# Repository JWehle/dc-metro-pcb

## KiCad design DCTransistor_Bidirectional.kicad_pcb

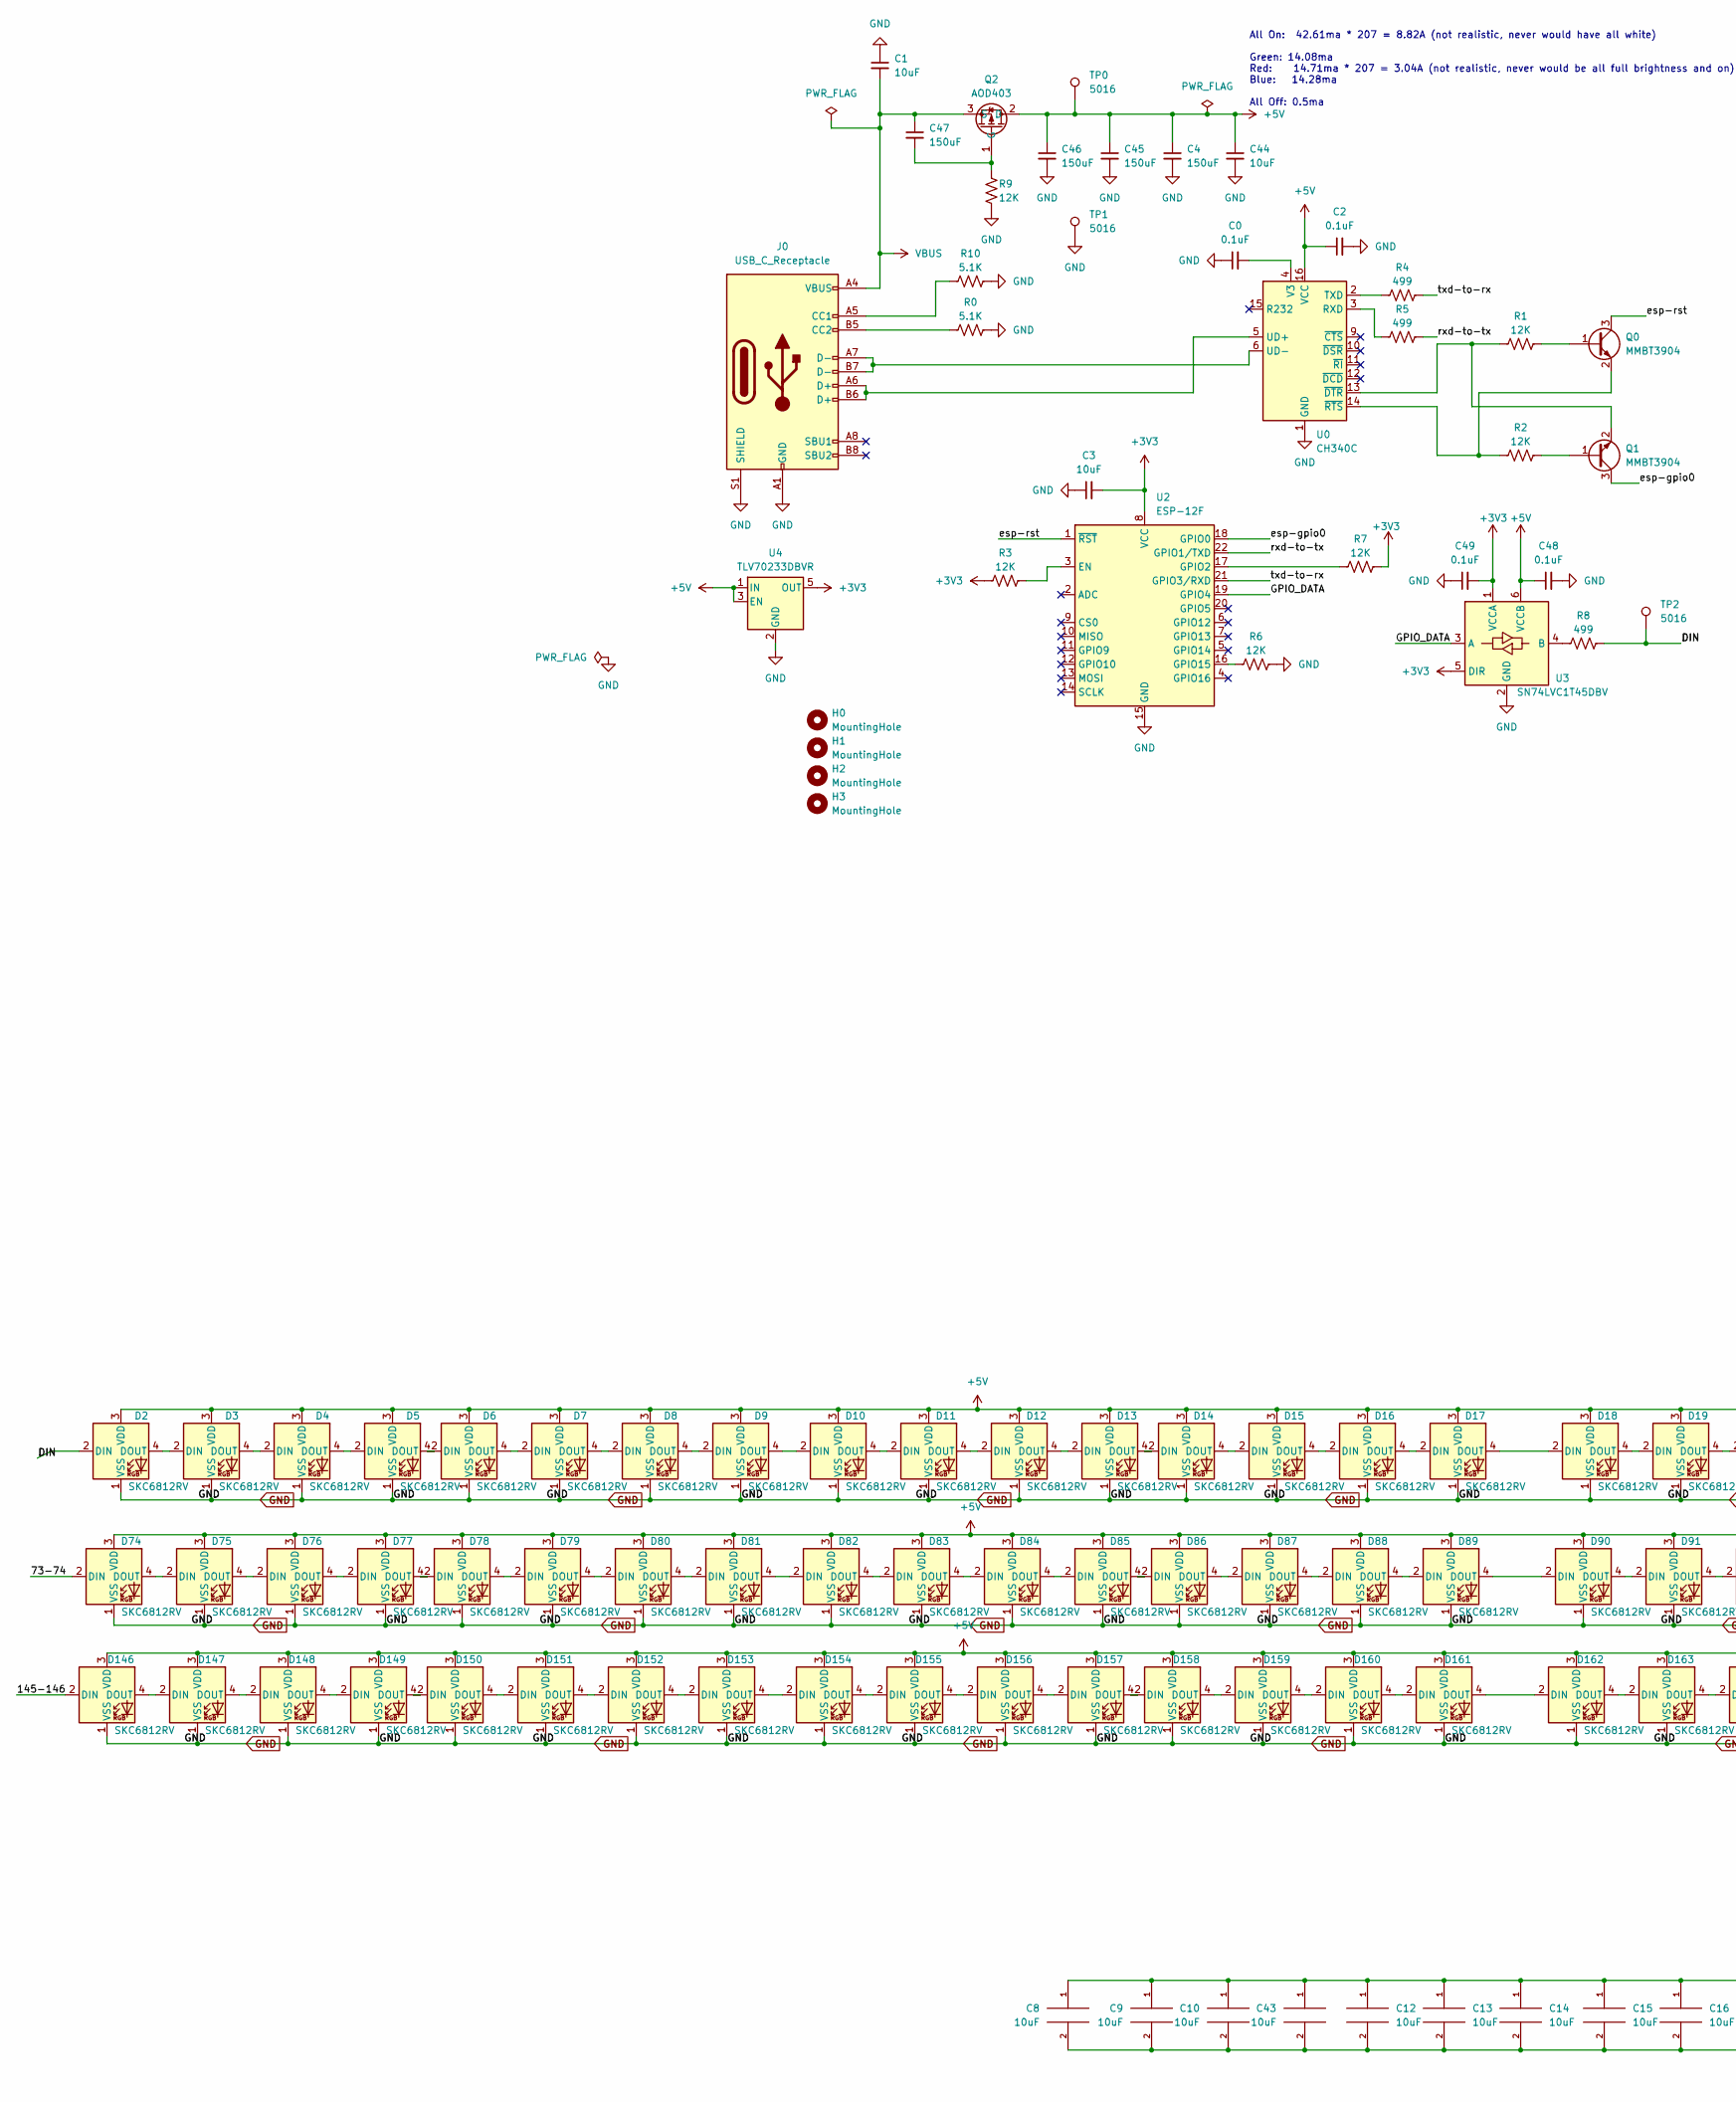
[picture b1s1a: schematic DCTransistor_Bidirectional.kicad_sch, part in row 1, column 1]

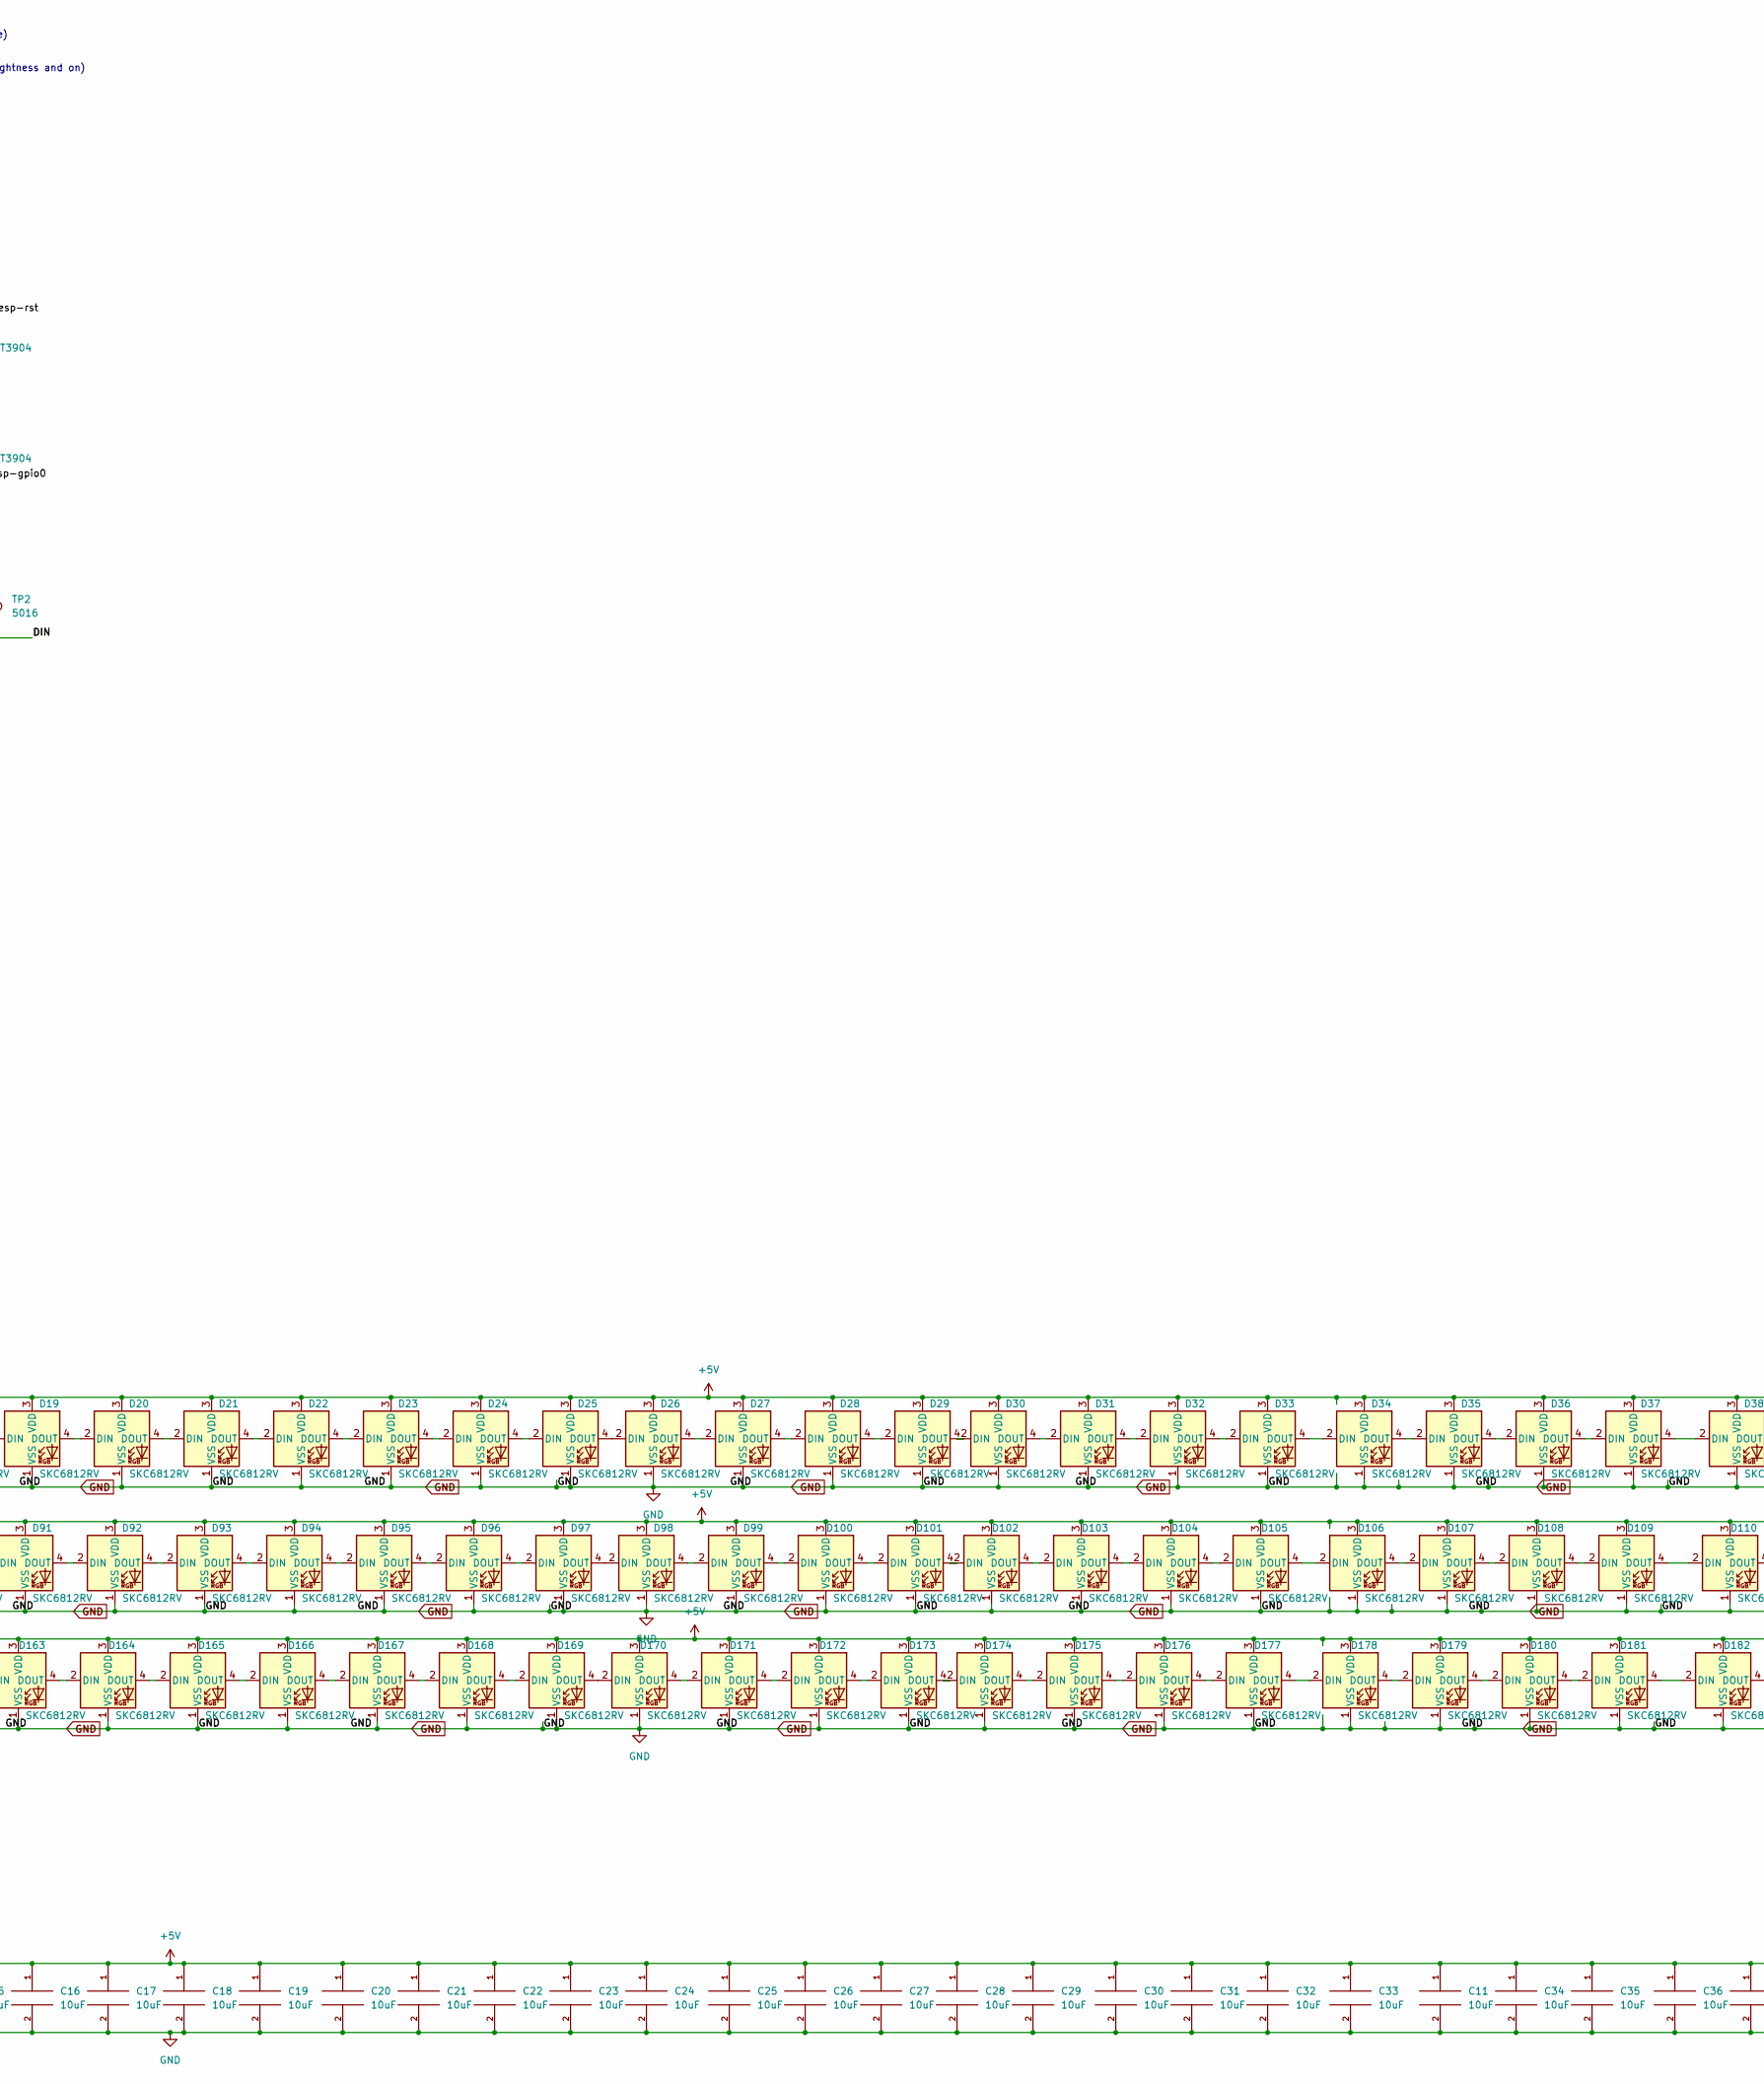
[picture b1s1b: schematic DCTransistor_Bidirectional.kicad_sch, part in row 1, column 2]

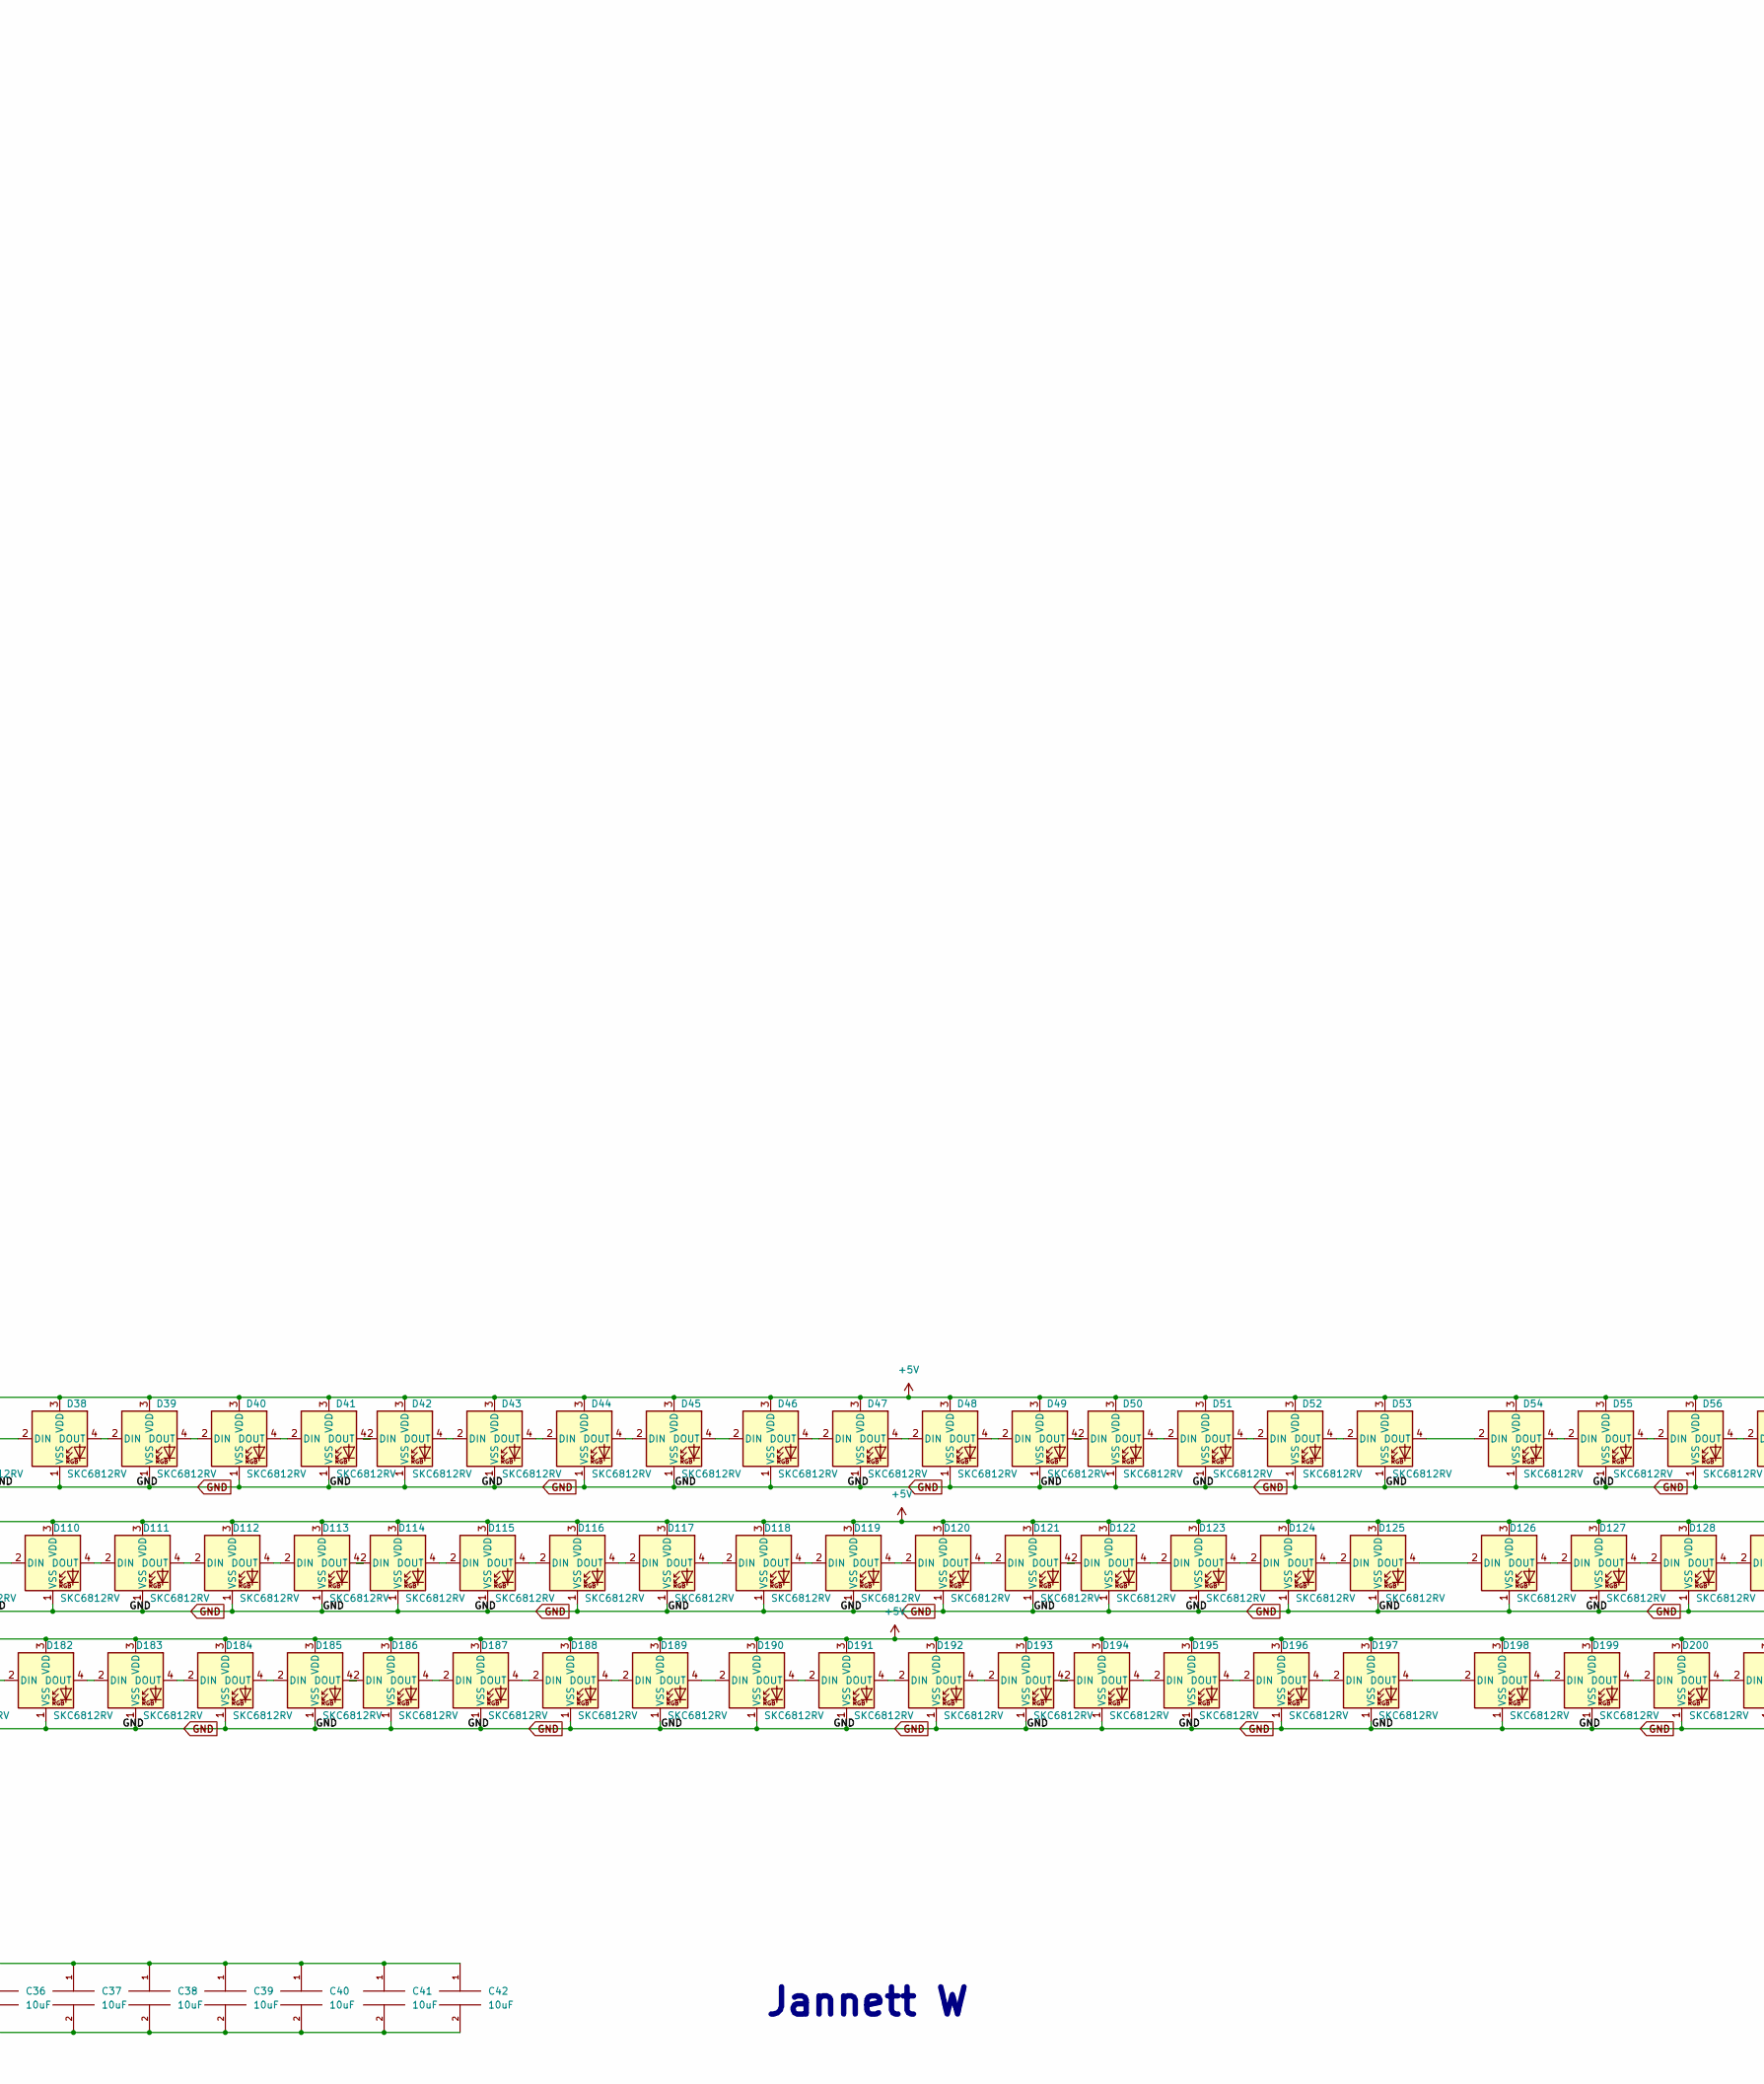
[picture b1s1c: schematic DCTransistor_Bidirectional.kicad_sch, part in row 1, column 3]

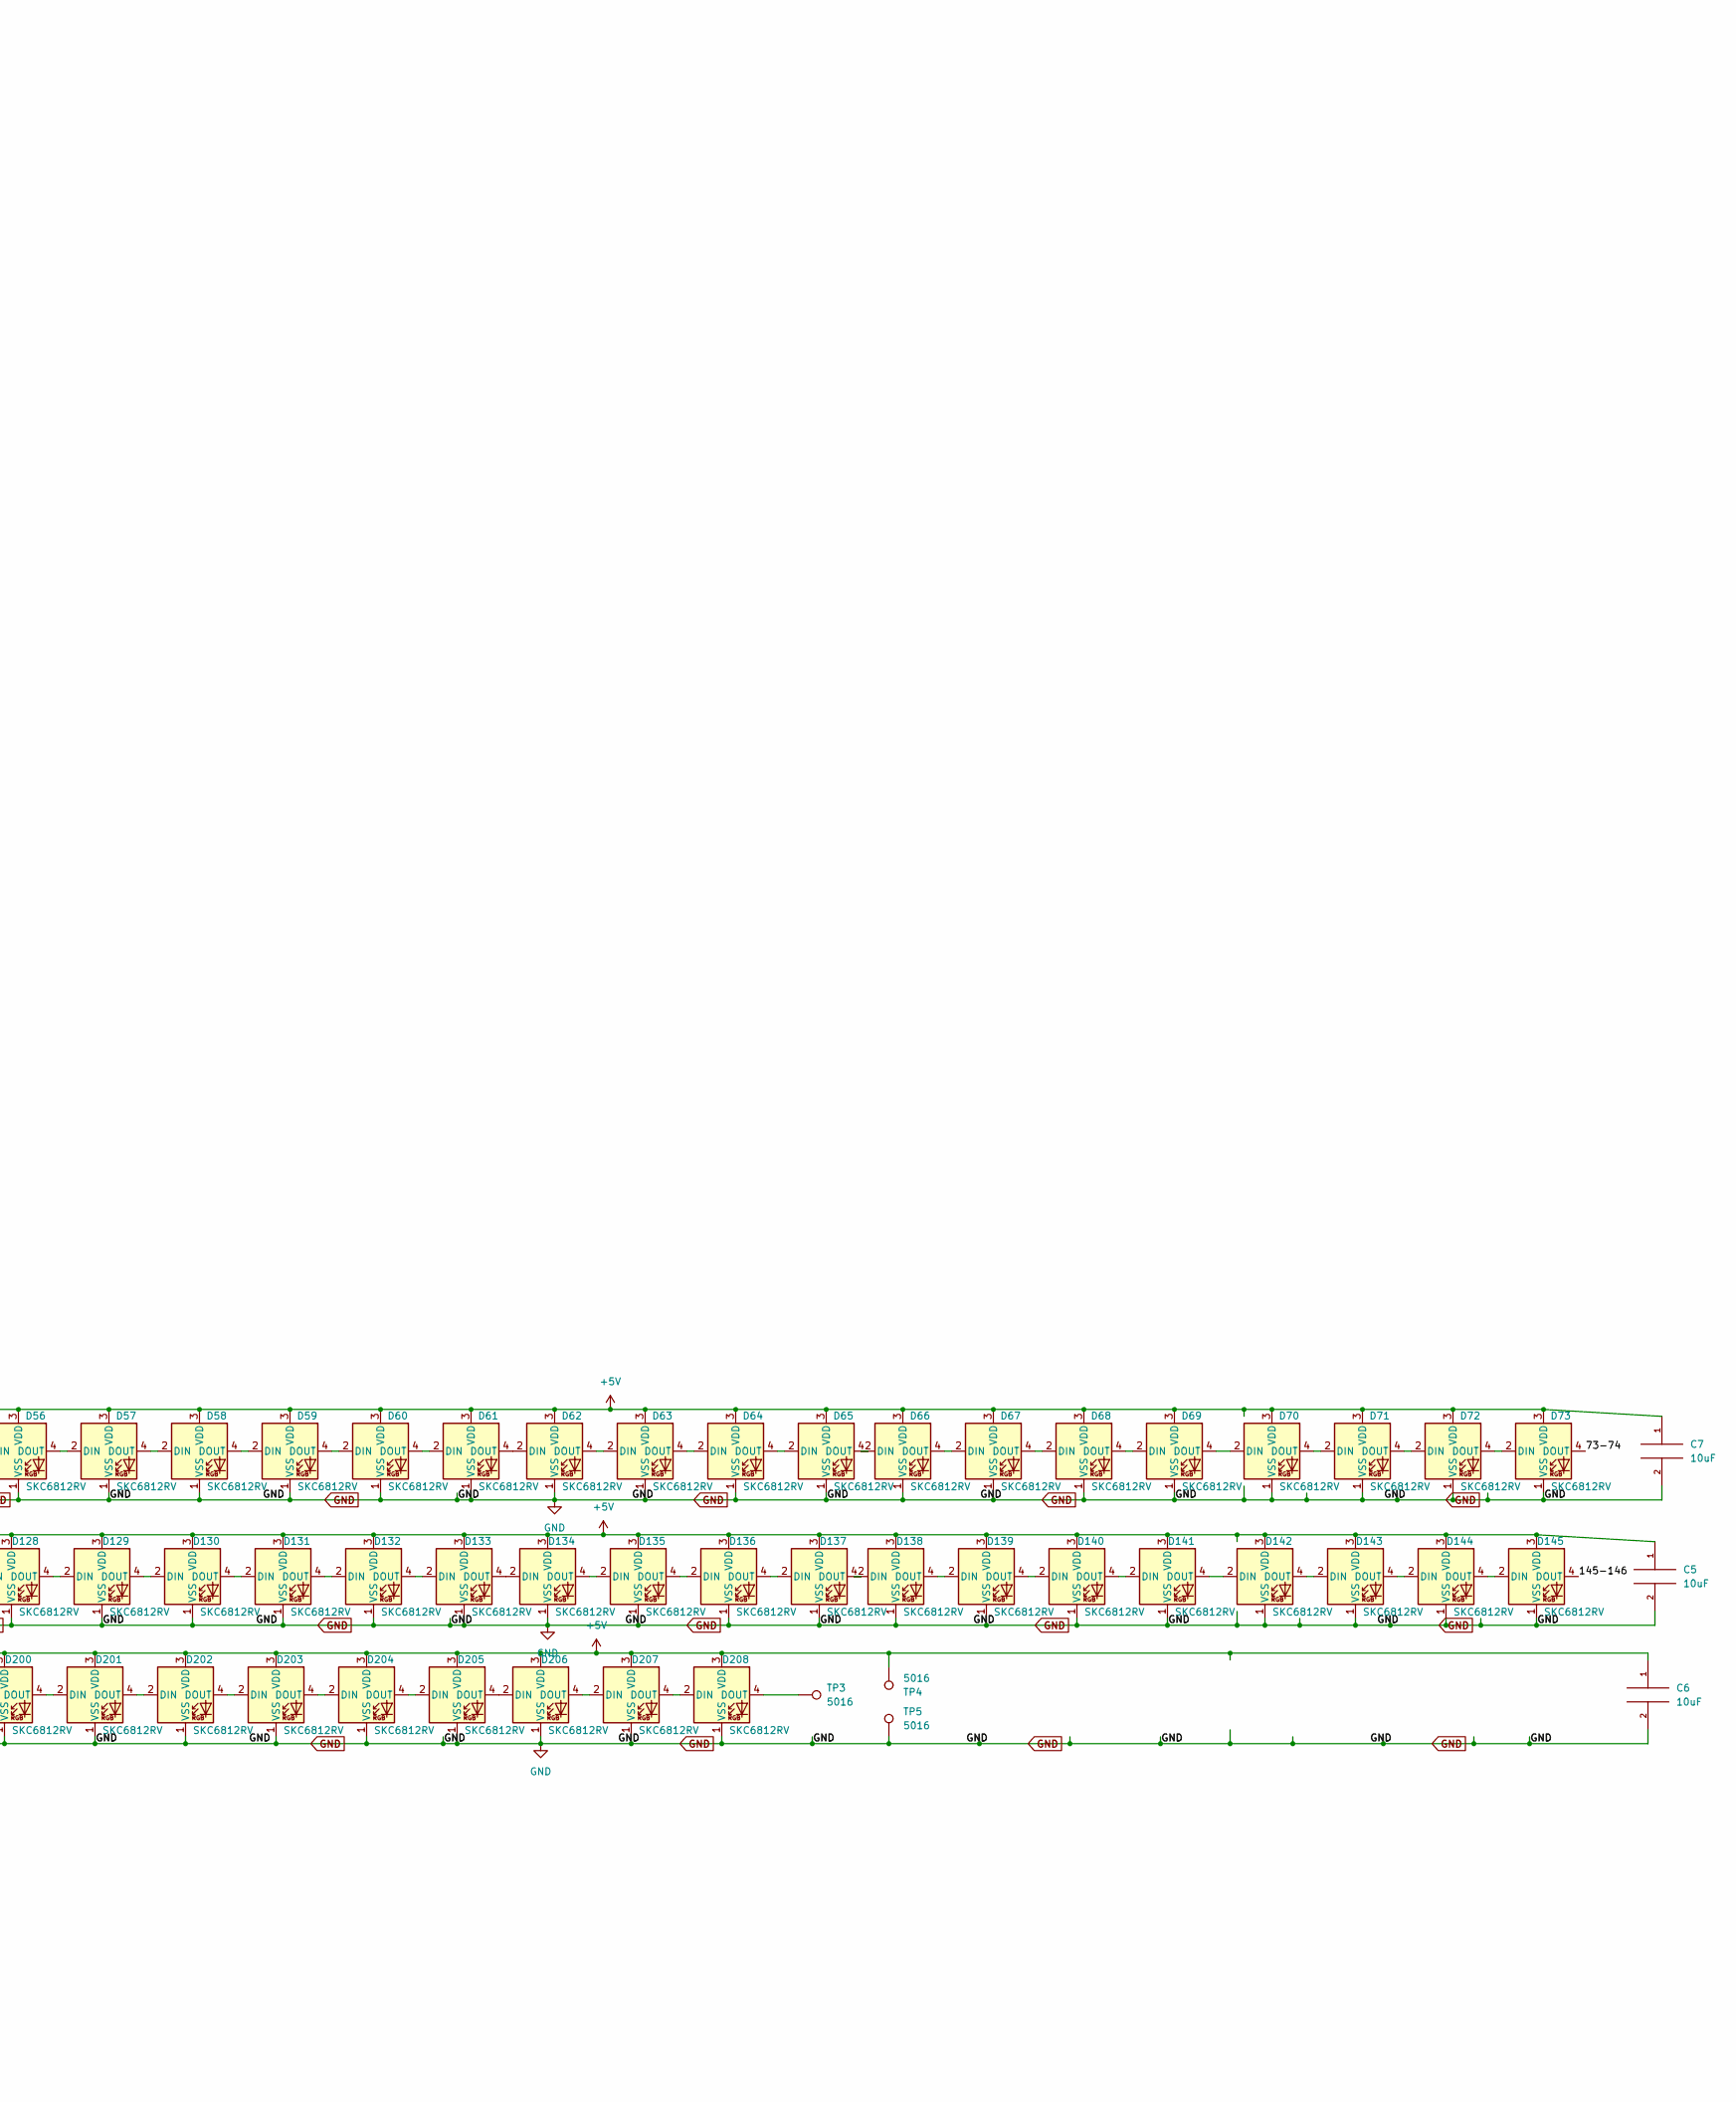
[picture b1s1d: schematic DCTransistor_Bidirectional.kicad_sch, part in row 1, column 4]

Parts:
C0, C2, C48, C49: 0.1uF; C_0603_1608Metric
C1, C3, C5, C6, C7, C8, C9, C10, C11, C12, C13, C14, C15, C16, C17, C18, C19, C20, C21, C22, C23, C24, C25, C26, C27, C28, C29, C30, C31, C32, C33, C34, C35, C36, C37, C38, C39, C40, C41, C42, C43, C44: 10uF; C_0603_1608Metric
C4, C45, C46, C47: 150uF; CP_EIA-7343-43_Kemet-X_Pad2.25x2.55mm_HandSolder
D2, D3, D4, D5, D6, D7, D8, D9, D10, D11, D12, D13, D14, D15, D16, D17, D18, D19, D20, D21, D22, D23, D24, D25, D26, D27, D28, D29, D30, D31, D32, D33, D34, D35, D36, D37, D38, D39, D40, D41, D42, D43, D44, D45, D46, D47, D48, D49, D50, D51, D52, D53, D54, D55, D56, D57, D58, D59, D60, D61, D62, D63, D64, D65, D66, D67, D68, D69, D70, D71, D72, D73, D74, D75, D76, D77, D78, D79, D80, D81, D82, D83, D84, D85, D86, D87, D88, D89, D90, D91, D92, D93, D94, D95, D96, D97, D98, D99, D100, D101, D102, D103, D104, D105, D106, D107, D108, D109, D110, D111, D112, D113, D114, D115, D116, D117, D118, D119, D120, D121, D122, D123, D124, D125, D126, D127, D128, D129, D130, D131, D132, D133, D134, D135, D136, D137, D138, D139, D140, D141, D142, D143, D144, D145, D146, D147, D148, D149, D150, D151, D152, D153, D154, D155, D156, D157, D158, D159, D160, D161, D162, D163, D164, D165, D166, D167, D168, D169, D170, D171, D172, D173, D174, D175, D176, D177, D178, D179, D180, D181, D182, D183, D184, D185, D186, D187, D188, D189, D190, D191, D192, D193, D194, D195, D196, D197, D198, D199, D200, D201, D202, D203, D204, D205, D206, D207, D208: SKC6812RV; LED_SK6812_PLCC4_5.0x5.0mm_P3.2mm_no_silk
H0, H1, H2, H3: MountingHole; MountingHole_6.4mm_M6
J0: USB_C_Receptacle; USB_C_Receptacle_GSB1C4621DS2HR
Q0, Q1: MMBT3904; SOT-23-3
Q2: AOD403; TO-252-2
R0, R10: 5.1K; R_0603_1608Metric
R1, R2, R3, R6, R7, R9: 12K; R_0603_1608Metric
R4, R5, R8: 499; R_0603_1608Metric
TP0, TP1, TP2, TP3, TP4, TP5: 5016; TestPoint_Keystone_5016_Compact
U0: CH340C; SOIC-16_3.9x9.9mm_P1.27mm
U2: ESP-12F; ESP-12E
U3: SN74LVC1T45DBV; SOT-23-6_Handsoldering
U4: TLV70233DBVR; SOT-23-5

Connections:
+3V3: C3.2, C49.2, R3.1, R7.2, U2.8 (VCC), U3.1 (VCCA), U3.5 (DIR), U4.5 (OUT)
+5V: C2.1, C4.1, C5.1, C6.1, C7.1, C8.1, C9.1, C10.1, C11.1, C12.1, C13.1, C14.1, C15.1, C16.1, C17.1, C18.1, C19.1, C20.1, C21.1, C22.1, C23.1, C24.1, C25.1, C26.1, C27.1, C28.1, C29.1, C30.1, C31.1, C32.1, C33.1, C34.1, C35.1, C36.1, C37.1, C38.1, C39.1, C40.1, C41.1, C42.1, C43.1, C44.1, C45.1, C46.1, C48.1, D2.3 (VDD), D3.3 (VDD), D4.3 (VDD), D5.3 (VDD), D6.3 (VDD), D7.3 (VDD), D8.3 (VDD), D9.3 (VDD), D10.3 (VDD), D11.3 (VDD), D12.3 (VDD), D13.3 (VDD), D14.3 (VDD), D15.3 (VDD), D16.3 (VDD), D17.3 (VDD), D18.3 (VDD), D19.3 (VDD), D20.3 (VDD), D21.3 (VDD), D22.3 (VDD), D23.3 (VDD), D24.3 (VDD), D25.3 (VDD), D26.3 (VDD), D27.3 (VDD), D28.3 (VDD), D29.3 (VDD), D30.3 (VDD), D31.3 (VDD), D32.3 (VDD), D33.3 (VDD), D34.3 (VDD), D35.3 (VDD), D36.3 (VDD), D37.3 (VDD), D38.3 (VDD), D39.3 (VDD), D40.3 (VDD), D41.3 (VDD), D42.3 (VDD), D43.3 (VDD), D44.3 (VDD), D45.3 (VDD), D46.3 (VDD), D47.3 (VDD), D48.3 (VDD), D49.3 (VDD), D50.3 (VDD), D51.3 (VDD), D52.3 (VDD), D53.3 (VDD), D54.3 (VDD)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
/73-74: D73.4 (DOUT), D74.2 (DIN)
/145-146: D145.4 (DOUT), D146.2 (DIN)
/DIN: D2.2 (DIN), R8.2, TP2.1
/GPIO_DATA: U2.19 (GPIO4), U3.3 (A)
/esp-gpio0: Q1.3 (C), U2.18 (GPIO0)
/esp-rst: Q0.3 (C), U2.1 (~RST)
/rxd-to-tx: R5.2, U2.22 (GPIO1/TXD)
/txd-to-rx: R4.2, U2.21 (GPIO3/RXD)
GND: C0.1, C1.1, C2.2, C3.1, C4.2, C5.2, C6.2, C7.2, C8.2, C9.2, C10.2, C11.2, C12.2, C13.2, C14.2, C15.2, C16.2, C17.2, C18.2, C19.2, C20.2, C21.2, C22.2, C23.2, C24.2, C25.2, C26.2, C27.2, C28.2, C29.2, C30.2, C31.2, C32.2, C33.2, C34.2, C35.2, C36.2, C37.2, C38.2, C39.2, C40.2, C41.2, C42.2, C43.2, C44.2, C45.2, C46.2, C48.2, C49.1, D2.1 (VSS), D3.1 (VSS), D4.1 (VSS), D5.1 (VSS), D6.1 (VSS), D7.1 (VSS), D8.1 (VSS), D9.1 (VSS), D10.1 (VSS), D11.1 (VSS), D12.1 (VSS), D13.1 (VSS), D14.1 (VSS), D15.1 (VSS), D16.1 (VSS), D17.1 (VSS), D18.1 (VSS), D19.1 (VSS), D20.1 (VSS), D21.1 (VSS), D22.1 (VSS), D23.1 (VSS), D24.1 (VSS), D25.1 (VSS), D26.1 (VSS), D27.1 (VSS), D28.1 (VSS), D29.1 (VSS), D30.1 (VSS), D31.1 (VSS), D32.1 (VSS), D33.1 (VSS), D34.1 (VSS), D35.1 (VSS), D36.1 (VSS), D37.1 (VSS), D38.1 (VSS), D39.1 (VSS), D40.1 (VSS), D41.1 (VSS), D42.1 (VSS), D43.1 (VSS), D44.1 (VSS), D45.1 (VSS), D46.1 (VSS), D47.1 (VSS), D48.1 (VSS), D49.1 (VSS), D50.1 (VSS)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
unnamed: D2.4 (DOUT), D3.2 (DIN)
unnamed: D3.4 (DOUT), D4.2 (DIN)
unnamed: D4.4 (DOUT), D5.2 (DIN)
unnamed: D5.4 (DOUT), D6.2 (DIN)
unnamed: D6.4 (DOUT), D7.2 (DIN)
unnamed: D7.4 (DOUT), D8.2 (DIN)
unnamed: D8.4 (DOUT), D9.2 (DIN)
unnamed: D9.4 (DOUT), D10.2 (DIN)
unnamed: D10.4 (DOUT), D11.2 (DIN)
unnamed: D11.4 (DOUT), D12.2 (DIN)
unnamed: D12.4 (DOUT), D13.2 (DIN)
unnamed: D13.4 (DOUT), D14.2 (DIN)
unnamed: D14.4 (DOUT), D15.2 (DIN)
unnamed: D15.4 (DOUT), D16.2 (DIN)
unnamed: D16.4 (DOUT), D17.2 (DIN)
unnamed: D17.4 (DOUT), D18.2 (DIN)
unnamed: D18.4 (DOUT), D19.2 (DIN)
unnamed: D19.4 (DOUT), D20.2 (DIN)
unnamed: D20.4 (DOUT), D21.2 (DIN)
unnamed: D21.4 (DOUT), D22.2 (DIN)
unnamed: D22.4 (DOUT), D23.2 (DIN)
unnamed: D23.4 (DOUT), D24.2 (DIN)
unnamed: D24.4 (DOUT), D25.2 (DIN)
unnamed: D25.4 (DOUT), D26.2 (DIN)
unnamed: D26.4 (DOUT), D27.2 (DIN)
unnamed: D27.4 (DOUT), D28.2 (DIN)
unnamed: D28.4 (DOUT), D29.2 (DIN)
unnamed: D29.4 (DOUT), D30.2 (DIN)
unnamed: D30.4 (DOUT), D31.2 (DIN)
unnamed: D31.4 (DOUT), D32.2 (DIN)
unnamed: D32.4 (DOUT), D33.2 (DIN)
unnamed: D33.4 (DOUT), D34.2 (DIN)
unnamed: D34.4 (DOUT), D35.2 (DIN)
unnamed: D35.4 (DOUT), D36.2 (DIN)
unnamed: D36.4 (DOUT), D37.2 (DIN)
unnamed: D37.4 (DOUT), D38.2 (DIN)
unnamed: D38.4 (DOUT), D39.2 (DIN)
unnamed: D39.4 (DOUT), D40.2 (DIN)
unnamed: D40.4 (DOUT), D41.2 (DIN)
unnamed: D41.4 (DOUT), D42.2 (DIN)
unnamed: D42.4 (DOUT), D43.2 (DIN)
unnamed: D43.4 (DOUT), D44.2 (DIN)
unnamed: D44.4 (DOUT), D45.2 (DIN)
unnamed: D45.4 (DOUT), D46.2 (DIN)
unnamed: D46.4 (DOUT), D47.2 (DIN)
unnamed: D47.4 (DOUT), D48.2 (DIN)
unnamed: D48.4 (DOUT), D49.2 (DIN)
unnamed: D49.4 (DOUT), D50.2 (DIN)
unnamed: D50.4 (DOUT), D51.2 (DIN)
unnamed: D51.4 (DOUT), D52.2 (DIN)
unnamed: D52.4 (DOUT), D53.2 (DIN)
unnamed: D53.4 (DOUT), D54.2 (DIN)
unnamed: D54.4 (DOUT), D55.2 (DIN)
unnamed: D55.4 (DOUT), D56.2 (DIN)
unnamed: D56.4 (DOUT), D57.2 (DIN)
unnamed: D57.4 (DOUT), D58.2 (DIN)
unnamed: D58.4 (DOUT), D59.2 (DIN)
unnamed: D59.4 (DOUT), D60.2 (DIN)
unnamed: D60.4 (DOUT), D61.2 (DIN)
unnamed: D61.4 (DOUT), D62.2 (DIN)
unnamed: D62.4 (DOUT), D63.2 (DIN)
unnamed: D63.4 (DOUT), D64.2 (DIN)
unnamed: D64.4 (DOUT), D65.2 (DIN)
unnamed: D65.4 (DOUT), D66.2 (DIN)
unnamed: D66.4 (DOUT), D67.2 (DIN)
unnamed: D67.4 (DOUT), D68.2 (DIN)
unnamed: D68.4 (DOUT), D69.2 (DIN)
unnamed: D69.4 (DOUT), D70.2 (DIN)
unnamed: D70.4 (DOUT), D71.2 (DIN)
unnamed: D71.4 (DOUT), D72.2 (DIN)
unnamed: D72.4 (DOUT), D73.2 (DIN)
unnamed: D74.4 (DOUT), D75.2 (DIN)
unnamed: D75.4 (DOUT), D76.2 (DIN)
unnamed: D76.4 (DOUT), D77.2 (DIN)
unnamed: D77.4 (DOUT), D78.2 (DIN)
unnamed: D78.4 (DOUT), D79.2 (DIN)
unnamed: D79.4 (DOUT), D80.2 (DIN)
unnamed: D80.4 (DOUT), D81.2 (DIN)
unnamed: D81.4 (DOUT), D82.2 (DIN)
unnamed: D82.4 (DOUT), D83.2 (DIN)
unnamed: D83.4 (DOUT), D84.2 (DIN)
unnamed: D84.4 (DOUT), D85.2 (DIN)
unnamed: D85.4 (DOUT), D86.2 (DIN)
unnamed: D86.4 (DOUT), D87.2 (DIN)
unnamed: D87.4 (DOUT), D88.2 (DIN)
unnamed: D88.4 (DOUT), D89.2 (DIN)
unnamed: D89.4 (DOUT), D90.2 (DIN)
unnamed: D90.4 (DOUT), D91.2 (DIN)
unnamed: D91.4 (DOUT), D92.2 (DIN)
unnamed: D92.4 (DOUT), D93.2 (DIN)
unnamed: D93.4 (DOUT), D94.2 (DIN)
unnamed: D94.4 (DOUT), D95.2 (DIN)
unnamed: D95.4 (DOUT), D96.2 (DIN)
unnamed: D96.4 (DOUT), D97.2 (DIN)
unnamed: D97.4 (DOUT), D98.2 (DIN)
unnamed: D98.4 (DOUT), D99.2 (DIN)
unnamed: D99.4 (DOUT), D100.2 (DIN)
unnamed: D100.4 (DOUT), D101.2 (DIN)
unnamed: D101.4 (DOUT), D102.2 (DIN)
unnamed: D102.4 (DOUT), D103.2 (DIN)
unnamed: D103.4 (DOUT), D104.2 (DIN)
unnamed: D104.4 (DOUT), D105.2 (DIN)
unnamed: D105.4 (DOUT), D106.2 (DIN)
unnamed: D106.4 (DOUT), D107.2 (DIN)
unnamed: D107.4 (DOUT), D108.2 (DIN)
unnamed: D108.4 (DOUT), D109.2 (DIN)
unnamed: D109.4 (DOUT), D110.2 (DIN)
unnamed: D110.4 (DOUT), D111.2 (DIN)
unnamed: D111.4 (DOUT), D112.2 (DIN)
unnamed: D112.4 (DOUT), D113.2 (DIN)
unnamed: D113.4 (DOUT), D114.2 (DIN)
unnamed: D114.4 (DOUT), D115.2 (DIN)
unnamed: D115.4 (DOUT), D116.2 (DIN)
unnamed: D116.4 (DOUT), D117.2 (DIN)
unnamed: D117.4 (DOUT), D118.2 (DIN)
unnamed: D118.4 (DOUT), D119.2 (DIN)
unnamed: D119.4 (DOUT), D120.2 (DIN)
unnamed: D120.4 (DOUT), D121.2 (DIN)
unnamed: D121.4 (DOUT), D122.2 (DIN)
unnamed: D122.4 (DOUT), D123.2 (DIN)
unnamed: D123.4 (DOUT), D124.2 (DIN)
unnamed: D124.4 (DOUT), D125.2 (DIN)
unnamed: D125.4 (DOUT), D126.2 (DIN)
unnamed: D126.4 (DOUT), D127.2 (DIN)
unnamed: D127.4 (DOUT), D128.2 (DIN)
unnamed: D128.4 (DOUT), D129.2 (DIN)
unnamed: D129.4 (DOUT), D130.2 (DIN)
unnamed: D130.4 (DOUT), D131.2 (DIN)
unnamed: D131.4 (DOUT), D132.2 (DIN)
unnamed: D132.4 (DOUT), D133.2 (DIN)
unnamed: D133.4 (DOUT), D134.2 (DIN)
unnamed: D134.4 (DOUT), D135.2 (DIN)
unnamed: D135.4 (DOUT), D136.2 (DIN)
unnamed: D136.4 (DOUT), D137.2 (DIN)
unnamed: D137.4 (DOUT), D138.2 (DIN)
unnamed: D138.4 (DOUT), D139.2 (DIN)
unnamed: D139.4 (DOUT), D140.2 (DIN)
unnamed: D140.4 (DOUT), D141.2 (DIN)
unnamed: D141.4 (DOUT), D142.2 (DIN)
unnamed: D142.4 (DOUT), D143.2 (DIN)
unnamed: D143.4 (DOUT), D144.2 (DIN)
unnamed: D144.4 (DOUT), D145.2 (DIN)
unnamed: D146.4 (DOUT), D147.2 (DIN)
unnamed: D147.4 (DOUT), D148.2 (DIN)
unnamed: D148.4 (DOUT), D149.2 (DIN)
unnamed: D149.4 (DOUT), D150.2 (DIN)
unnamed: D150.4 (DOUT), D151.2 (DIN)
unnamed: D151.4 (DOUT), D152.2 (DIN)
unnamed: D152.4 (DOUT), D153.2 (DIN)
unnamed: D153.4 (DOUT), D154.2 (DIN)
unnamed: D154.4 (DOUT), D155.2 (DIN)
unnamed: D155.4 (DOUT), D156.2 (DIN)
unnamed: D156.4 (DOUT), D157.2 (DIN)
unnamed: D157.4 (DOUT), D158.2 (DIN)
unnamed: D158.4 (DOUT), D159.2 (DIN)
unnamed: D159.4 (DOUT), D160.2 (DIN)
unnamed: D160.4 (DOUT), D161.2 (DIN)
unnamed: D161.4 (DOUT), D162.2 (DIN)
unnamed: D162.4 (DOUT), D163.2 (DIN)
unnamed: D163.4 (DOUT), D164.2 (DIN)
unnamed: D164.4 (DOUT), D165.2 (DIN)
unnamed: D165.4 (DOUT), D166.2 (DIN)
unnamed: D166.4 (DOUT), D167.2 (DIN)
unnamed: D167.4 (DOUT), D168.2 (DIN)
unnamed: D168.4 (DOUT), D169.2 (DIN)
unnamed: D169.4 (DOUT), D170.2 (DIN)
unnamed: D170.4 (DOUT), D171.2 (DIN)
unnamed: D171.4 (DOUT), D172.2 (DIN)
unnamed: D172.4 (DOUT), D173.2 (DIN)
unnamed: D173.4 (DOUT), D174.2 (DIN)
unnamed: D174.4 (DOUT), D175.2 (DIN)
unnamed: D175.4 (DOUT), D176.2 (DIN)
unnamed: D176.4 (DOUT), D177.2 (DIN)
unnamed: D177.4 (DOUT), D178.2 (DIN)
unnamed: D178.4 (DOUT), D179.2 (DIN)
unnamed: D179.4 (DOUT), D180.2 (DIN)
unnamed: D180.4 (DOUT), D181.2 (DIN)
unnamed: D181.4 (DOUT), D182.2 (DIN)
unnamed: D182.4 (DOUT), D183.2 (DIN)
unnamed: D183.4 (DOUT), D184.2 (DIN)
unnamed: D184.4 (DOUT), D185.2 (DIN)
unnamed: D185.4 (DOUT), D186.2 (DIN)
unnamed: D186.4 (DOUT), D187.2 (DIN)
unnamed: D187.4 (DOUT), D188.2 (DIN)
unnamed: D188.4 (DOUT), D189.2 (DIN)
unnamed: D189.4 (DOUT), D190.2 (DIN)
unnamed: D190.4 (DOUT), D191.2 (DIN)
unnamed: D191.4 (DOUT), D192.2 (DIN)
unnamed: D192.4 (DOUT), D193.2 (DIN)
unnamed: D193.4 (DOUT), D194.2 (DIN)
unnamed: D194.4 (DOUT), D195.2 (DIN)
unnamed: D195.4 (DOUT), D196.2 (DIN)
unnamed: D196.4 (DOUT), D197.2 (DIN)
unnamed: D197.4 (DOUT), D198.2 (DIN)
unnamed: D198.4 (DOUT), D199.2 (DIN)
unnamed: D199.4 (DOUT), D200.2 (DIN)
unnamed: D200.4 (DOUT), D201.2 (DIN)
unnamed: D201.4 (DOUT), D202.2 (DIN)
unnamed: D202.4 (DOUT), D203.2 (DIN)
unnamed: D203.4 (DOUT), D204.2 (DIN)
unnamed: D204.4 (DOUT), D205.2 (DIN)
unnamed: D205.4 (DOUT), D206.2 (DIN)
unnamed: D206.4 (DOUT), D207.2 (DIN)
unnamed: D207.4 (DOUT), D208.2 (DIN)
unnamed: D208.4 (DOUT), TP3.1
unnamed: J0.A5 (CC1), R10.1
unnamed: J0.B5 (CC2), R0.1
unnamed: Q0.1 (B), R1.2
unnamed: Q0.2 (E), R2.1, U0.14 (~RTS)
unnamed: Q1.1 (B), R2.2
unnamed: Q1.2 (E), R1.1, U0.13 (~DTR)
unnamed: C47.2, Q2.1 (G), R9.1
unnamed: R5.1, U0.3 (RXD)
unnamed: R4.1, U0.2 (TXD)
unnamed: J0.A6 (D+), J0.B6 (D+), U0.5 (UD+)
unnamed: J0.A7 (D-), J0.B7 (D-), U0.6 (UD-)
unnamed: C0.2, U0.4 (V3)
unnamed: R3.2, U2.3 (EN)
unnamed: R7.1, U2.17 (GPIO2)
unnamed: R6.1, U2.16 (GPIO15)
unnamed: R8.1, U3.4 (B)
VBUS: C1.2, C47.1, J0.A4 (VBUS), J0.A9 (VBUS), J0.B4 (VBUS), J0.B9 (VBUS), Q2.3 (S)

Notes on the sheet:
All On: 42.61ma * 207 = 8.82A (not realistic, never would have all white) Green: 14.08ma Red: 14.71ma * 207 = 3.04A (not realistic, never would be all full brightness and on) Blue: 14.28ma All Off: 0.5ma
Jannett W

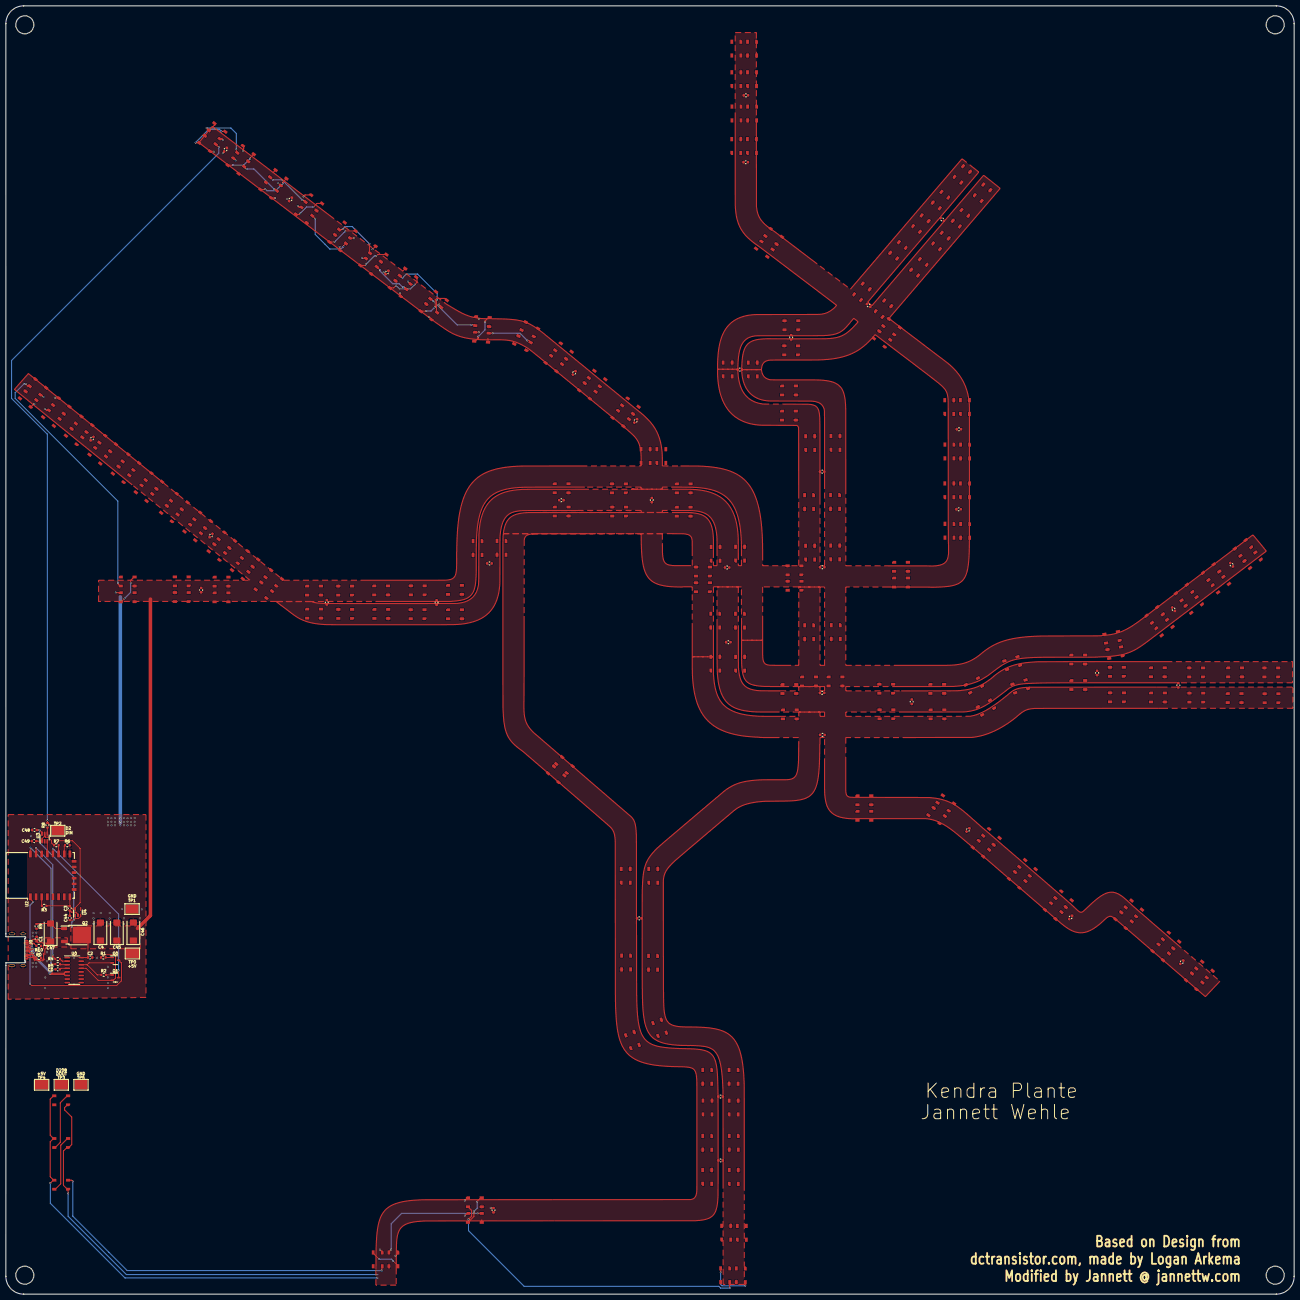
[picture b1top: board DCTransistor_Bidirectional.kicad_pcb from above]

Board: 2 copper layers, 457.2 x 457.2 mm, 286 parts (0 on the bottom side), 233 nets.

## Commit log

2025-01-25 schematic changes
2025-02-03 removed graphic temporarily for layout
2025-02-08 recentered pcb
2025-02-08 layout edits
2025-02-09 layout and footprint changes
2025-02-10 more layout updates
2025-03-16 layout fixes and schematic re-sync with layout
2025-03-16 layout updates
